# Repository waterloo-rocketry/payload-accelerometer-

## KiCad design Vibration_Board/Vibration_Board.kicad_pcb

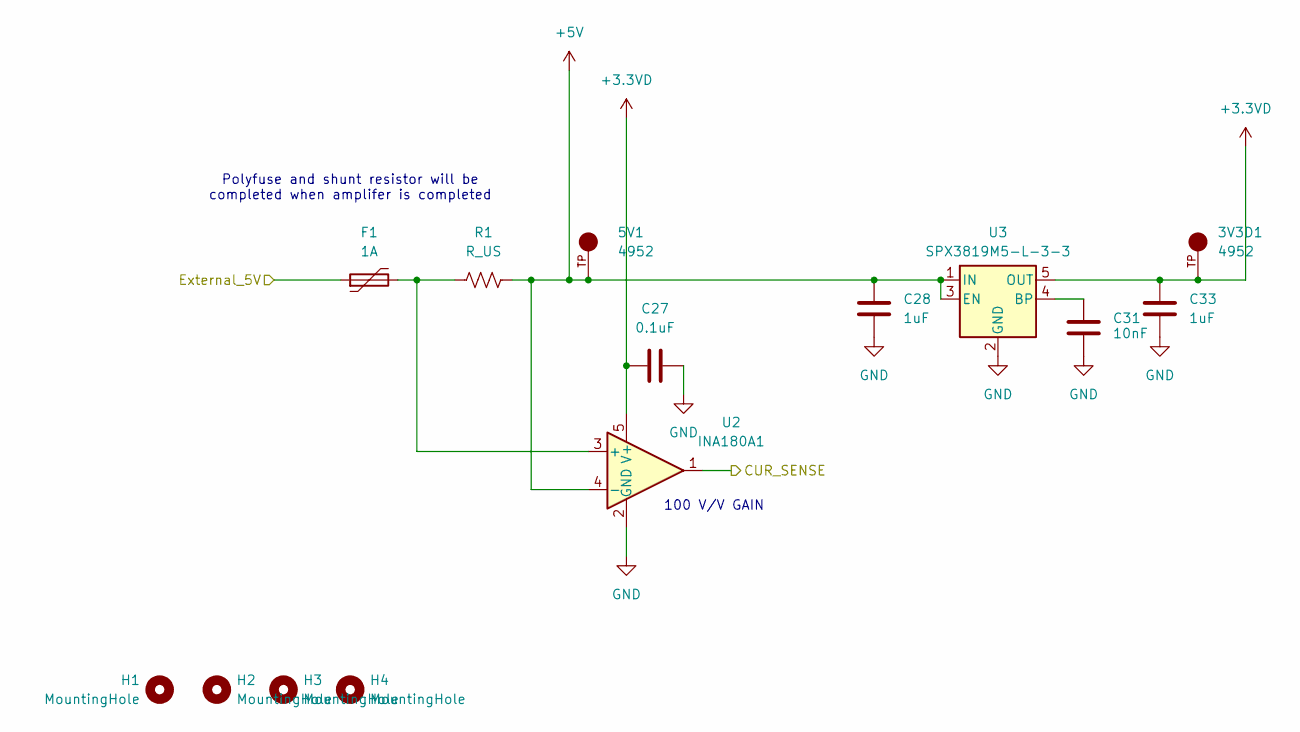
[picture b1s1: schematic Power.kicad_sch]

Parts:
3V3D1, 5V1: 4952; KEYSTONE_4952; PARTREV A
C27: 0.1uF; C_0805_2012Metric_Pad1.18x1.45mm_HandSolder
C28, C33: 1uF; C_0805_2012Metric_Pad1.18x1.45mm_HandSolder
C31: 10nF; C_0805_2012Metric_Pad1.18x1.45mm_HandSolder
F1: 1A; C_0805_2012Metric_Pad1.18x1.45mm_HandSolder
H1, H2, H3, H4: MountingHole; MountingHole_3.2mm_M3_ISO7380_Pad_TopBottom
R1: R_US; R_0805_2012Metric_Pad1.20x1.40mm_HandSolder
U2: INA180A1; SOT-23-5
U3: SPX3819M5-L-3-3; SOT-23-5

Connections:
+3.3VD: 3V3D1.TP, C27.1, C33.1, U2.5 (V+), U3.5 (OUT); also elsewhere on the board
+5V: 5V1.TP, C28.1, R1.2, U2.4 (-), U3.1 (IN), U3.3 (EN); also elsewhere on the board
/CUR_SEN: U2.1; also elsewhere on the board
/EXT_5V: F1.1; also elsewhere on the board
GND: C27.2, C28.2, C31.2, C33.2, U2.2 (GND), U3.2 (GND); also elsewhere on the board
unnamed: F1.2, R1.1, U2.3 (+)
unnamed: C31.1, U3.4 (BP)

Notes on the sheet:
100 V/V GAIN
Polyfuse and shunt resistor will be completed when amplifer is completed

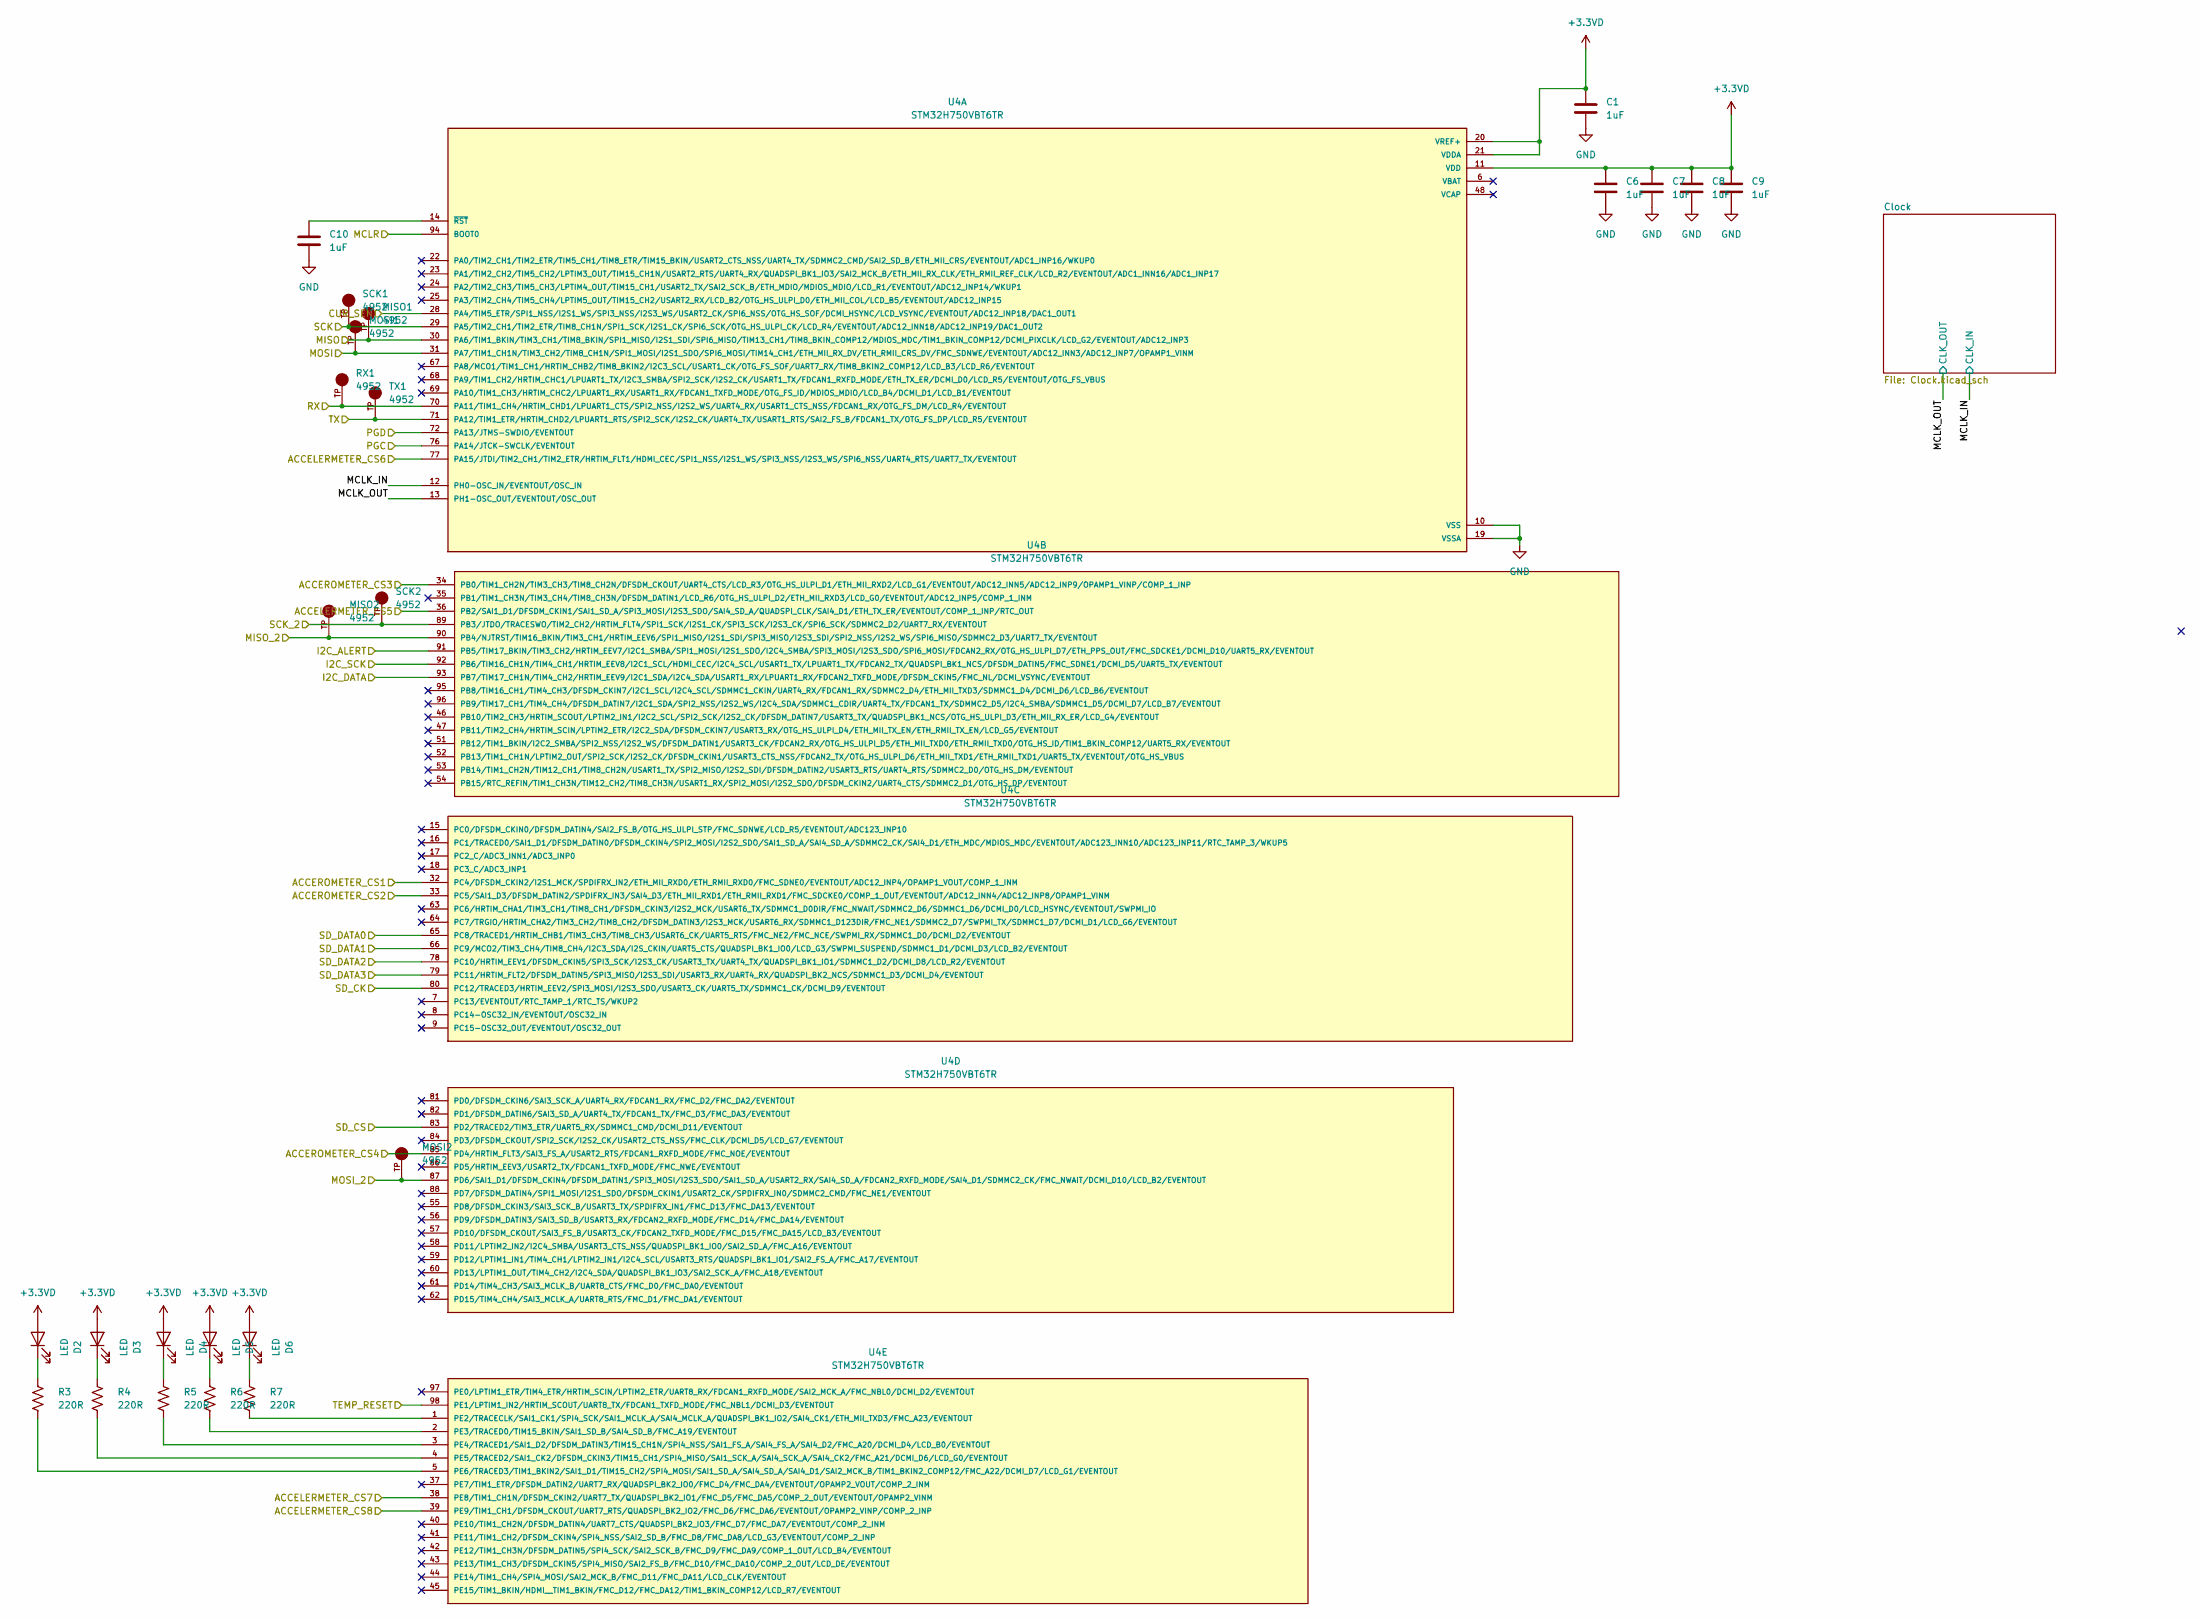
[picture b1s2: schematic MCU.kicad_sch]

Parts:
C1, C6, C7, C8, C9, C10: 1uF; C_0805_2012Metric_Pad1.18x1.45mm_HandSolder
D2, D3, D4, D5, D6: LED; LED_1206_3216Metric_Pad1.42x1.75mm_HandSolder
MISO1, MISO2: 4952; KEYSTONE_4952; PARTREV A
MOSI1, MOSI2: 4952; KEYSTONE_4952; PARTREV A
R3, R4, R5, R6, R7: 220R; R_0805_2012Metric_Pad1.20x1.40mm_HandSolder
RX1: 4952; KEYSTONE_4952; PARTREV A
SCK1, SCK2: 4952; KEYSTONE_4952; PARTREV A
TX1: 4952; KEYSTONE_4952; PARTREV A
U4: STM32H750VBT6TR; QFP50P1600X1600X160-100N; PARTREV 2

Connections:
+3.3VD: C1.1, C6.1, C7.1, C8.1, C9.1, D2.2 (A), D3.2 (A), D4.2 (A), D5.2 (A), D6.2 (A), U4.11 (VDD), U4.20 (VREF+), U4.21 (VDDA), U4.27 (VDD), U4.50 (VDD), U4.75 (VDD), U4.100 (VDD); also elsewhere on the board
/ACCEL_CS1: U4.32 (PC4/DFSDM_CKIN2/I2S1_MCK/SPDIFRX_IN2/ET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); also elsewhere on the board
/ACCEL_CS2: U4.33 (PC5/SAI1_D3/DFSDM_DATIN2/SPDIFRX_IN3/SA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); also elsewhere on the board
/ACCEL_CS3: U4.34 (PB0/TIM1_CH2N/TIM3_CH3/TIM8_CH2N/DFSDM_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); also elsewhere on the board
/ACCEL_CS4: U4.85 (PD4/HRTIM_FLT3/SAI3_FS_A/USART2_RTS/FDC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); also elsewhere on the board
/ACCEL_CS5: U4.36 (PB2/SAI1_D1/DFSDM_CKIN1/SAI1_SD_A/SPI3_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); also elsewhere on the board
/ACCEL_CS6: U4.77 (PA15/JTDI/TIM2_CH1/TIM2_ETR/HRTIM_FLT1/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); also elsewhere on the board
/ACCEL_CS7: U4.38 (PE8/TIM1_CH1N/DFSDM_CKIN2/UART7_TX/QUAD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); also elsewhere on the board
/ACCEL_CS8: U4.39 (PE9/TIM1_CH1/DFSDM_CKOUT/UART7_RTS/QUAD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); also elsewhere on the board
/CUR_SEN: U4.28 (PA4/TIM5_ETR/SPI1_NSS/I2S1_WS/SPI3_NSS/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); also elsewhere on the board
/Connectors/DATA1: U4.65 (PC8/TRACED1/HRTIM_CHB1/TIM3_CH3/TIM8_CH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); also elsewhere on the board
/Connectors/DATA2: U4.66 (PC9/MCO2/TIM3_CH4/TIM8_CH4/I2C3_SDA/I2S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); also elsewhere on the board
/Connectors/DATA3: U4.78 (PC10/HRTIM_EEV1/DFSDM_CKIN5/SPI3_SCK/I2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); also elsewhere on the board
/Connectors/DATA4: U4.79 (PC11/HRTIM_FLT2/DFSDM_DATIN5/SPI3_MISO/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); also elsewhere on the board
/Connectors/MISO_2: MISO2.TP, U4.90 (PB4/NJTRST/TIM16_BKIN/TIM3_CH1/HRTIM_EE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); also elsewhere on the board
/Connectors/MOSI_2: MOSI2.TP, U4.87 (PD6/SAI1_D1/DFSDM_CKIN4/DFSDM_DATIN1/SP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); also elsewhere on the board
/Connectors/SCK_2: SCK2.TP, U4.89 (PB3/JTDO/TRACESWO/TIM2_CH2/HRTIM_FLT4/S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); also elsewhere on the board
/Connectors/SD_CLK: U4.80 (PC12/TRACED3/HRTIM_EEV2/SPI3_MOSI/I2S3_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); also elsewhere on the board
/Connectors/SD_CS: U4.83 (PD2/TRACED2/TIM3_ETR/UART5_RX/SDMMC1_CM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); also elsewhere on the board
/I2C_ALERT: U4.91 (PB5/TIM17_BKIN/TIM3_CH2/HRTIM_EEV7/I2C1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); also elsewhere on the board
/I2C_DATA: U4.93 (PB7/TIM17_CH1N/TIM4_CH2/HRTIM_EEV9/I2C1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); also elsewhere on the board
/I2C_SCK: U4.92 (PB6/TIM16_CH1N/TIM4_CH1/HRTIM_EEV8/I2C1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); also elsewhere on the board
/MCLR: U4.94 (BOOT0); also elsewhere on the board
/MCU/MCLK_IN: U4.12 (PH0-OSC_IN/EVENTOUT/OSC_IN); also elsewhere on the board
/MCU/MCLK_OUT: U4.13 (PH1-OSC_OUT/EVENTOUT/OSC_OUT); also elsewhere on the board
/MISO: MISO1.TP, U4.30 (PA6/TIM1_BKIN/TIM3_CH1/TIM8_BKIN/SPI1_M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); also elsewhere on the board
/MOSI: MOSI1.TP, U4.31 (PA7/TIM1_CH1N/TIM3_CH2/TIM8_CH1N/SPI1_M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); also elsewhere on the board
/PGC: U4.72 (PA13/JTMS-SWDIO/EVENTOUT); also elsewhere on the board
/PGD: U4.76 (PA14/JTCK-SWCLK/EVENTOUT); also elsewhere on the board
/RX: RX1.TP, U4.70 (PA11/TIM1_CH4/HRTIM_CHD1/LPUART1_CTS/SP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); also elsewhere on the board
/SCK: SCK1.TP, U4.29 (PA5/TIM2_CH1/TIM2_ETR/TIM8_CH1N/SPI1_SC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); also elsewhere on the board
/SENSOR_RESET: U4.98 (PE1/LPTIM1_IN2/HRTIM_SCOUT/UART8_TX/FDC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); also elsewhere on the board
/TX: TX1.TP, U4.71 (PA12/TIM1_ETR/HRTIM_CHD2/LPUART1_RTS/SP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); also elsewhere on the board
GND: C1.2, C6.2, C7.2, C8.2, C9.2, C10.2, U4.10 (VSS), U4.19 (VSSA), U4.26 (VSS), U4.49 (VSS), U4.74 (VSS), U4.99 (VSS); also elsewhere on the board
unnamed: D2.1 (K), R3.1
unnamed: D3.1 (K), R4.1
unnamed: D4.1 (K), R5.1
unnamed: D5.1 (K), R6.1
unnamed: D6.1 (K), R7.1
unnamed: C10.1, U4.14 (~RST)
unnamed: R7.2, U4.1 (PE2/TRACECLK/SAI1_CK1/SPI4_SCK/SAI1_MCL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)
unnamed: R6.2, U4.2 (PE3/TRACED0/TIM15_BKIN/SAI1_SD_B/SAI4_S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)
unnamed: R5.2, U4.3 (PE4/TRACED1/SAI1_D2/DFSDM_DATIN3/TIM15_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)
unnamed: R4.2, U4.4 (PE5/TRACED2/SAI1_CK2/DFSDM_CKIN3/TIM15_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)
unnamed: R3.2, U4.5 (PE6/TRACED3/TIM1_BKIN2/SAI1_D1/TIM15_CH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)

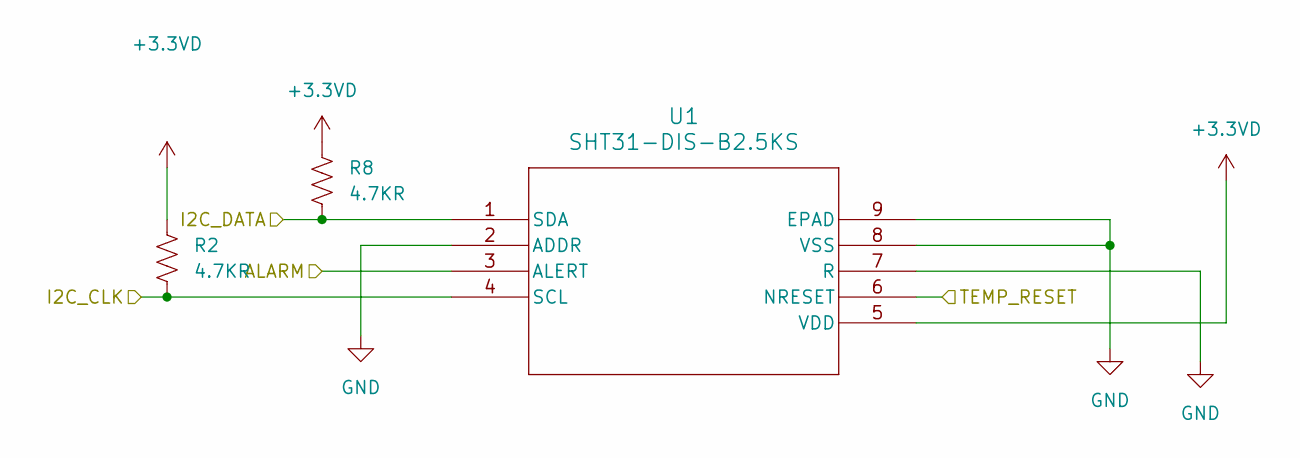
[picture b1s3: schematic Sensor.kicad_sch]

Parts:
R2, R8: 4.7KR; R_0805_2012Metric_Pad1.20x1.40mm_HandSolder
U1: SHT31-DIS-B2.5KS; U_SHT3_SEN-M

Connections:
+3.3VD: R2.1, R8.1, U1.5 (VDD); also elsewhere on the board
/I2C_ALERT: U1.3 (ALERT); also elsewhere on the board
/I2C_DATA: R8.2, U1.1 (SDA); also elsewhere on the board
/I2C_SCK: R2.2, U1.4 (SCL); also elsewhere on the board
/SENSOR_RESET: U1.6 (NRESET); also elsewhere on the board
GND: U1.2 (ADDR), U1.7 (R), U1.8 (VSS), U1.9 (EPAD); also elsewhere on the board

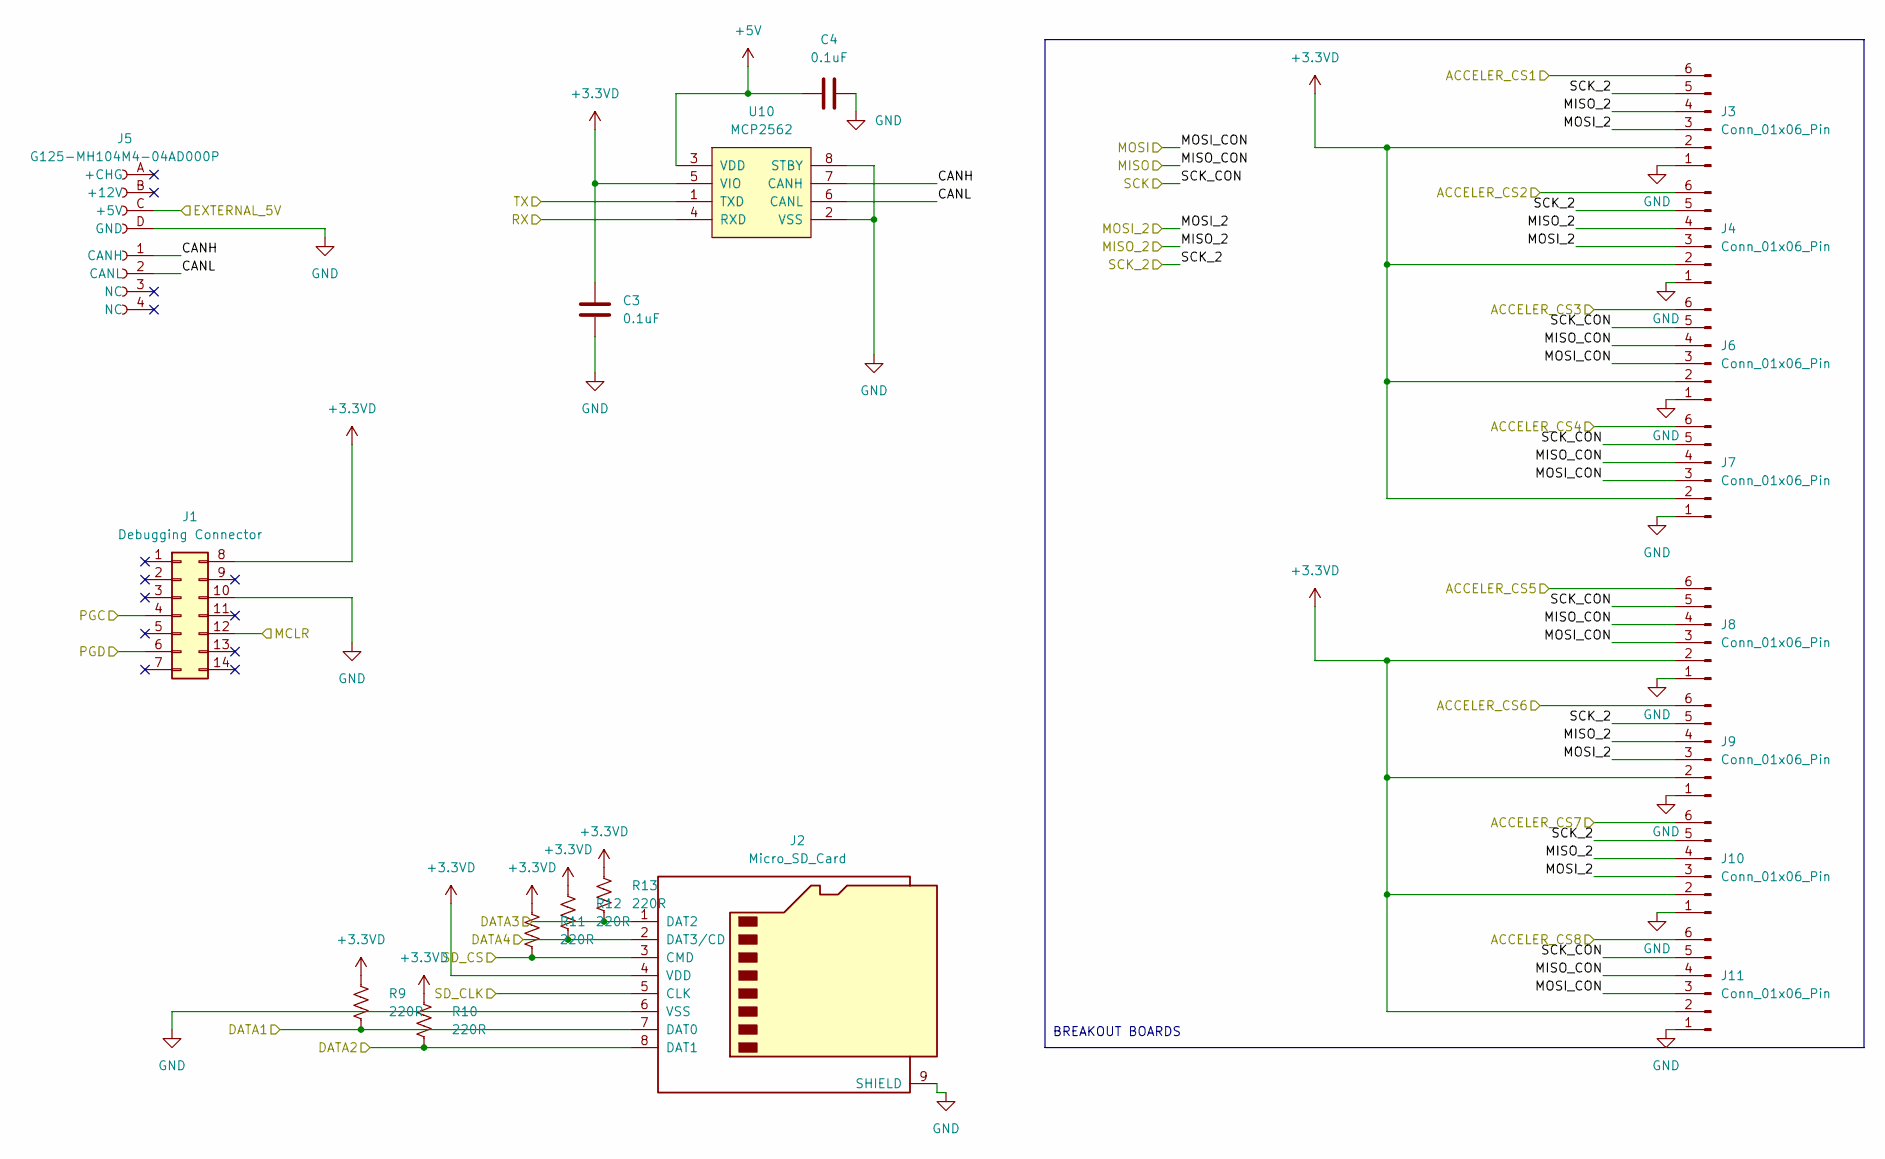
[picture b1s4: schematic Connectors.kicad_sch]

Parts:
C3, C4: 0.1uF; C_0805_2012Metric_Pad1.18x1.45mm_HandSolder
J1: Debugging Connector; PinHeader_2x07_P1.27mm_Vertical_SMD
J2: Micro_SD_Card; microSD_Molex_WM6698CT-ND
J3, J4, J6, J7, J8, J9, J10, J11: Conn_01x06_Pin; CONN6_S6B-PH_JST
J5: G125-MH104M4-04AD000P; connector_Harwin_G125-MH104M4-04AD000P
R9, R10, R11, R12, R13: 220R; R_0805_2012Metric_Pad1.20x1.40mm_HandSolder
U10: MCP2562; SOIC-8_3.9x4.9mm_P1.27mm

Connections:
+3.3VD: C3.2, J1.8, J2.4 (VDD), J3.2, J4.2, J6.2, J7.2, J8.2, J9.2, J10.2, J11.2, R9.1, R10.1, R11.1, R12.1, R13.1, U10.5 (VIO); also elsewhere on the board
+5V: C4.1, U10.3 (VDD); also elsewhere on the board
/ACCEL_CS1: J7.6; also elsewhere on the board
/ACCEL_CS2: J6.6; also elsewhere on the board
/ACCEL_CS3: J4.6; also elsewhere on the board
/ACCEL_CS4: J3.6; also elsewhere on the board
/ACCEL_CS5: J8.6; also elsewhere on the board
/ACCEL_CS6: J9.6; also elsewhere on the board
/ACCEL_CS7: J10.6; also elsewhere on the board
/ACCEL_CS8: J11.6; also elsewhere on the board
/Connectors/CANH: J5.1 (CANH), U10.7 (CANH)
/Connectors/CANL: J5.2 (CANL), U10.6 (CANL)
/Connectors/DATA1: J2.7 (DAT0), R9.2; also elsewhere on the board
/Connectors/DATA2: J2.8 (DAT1), R10.2; also elsewhere on the board
/Connectors/DATA3: J2.1 (DAT2), R13.2; also elsewhere on the board
/Connectors/DATA4: J2.2 (DAT3/CD), R12.2; also elsewhere on the board
/Connectors/MISO_2: J3.4, J4.4, J9.4, J10.4; also elsewhere on the board
/Connectors/MOSI_2: J3.3, J4.3, J9.3, J10.3; also elsewhere on the board
/Connectors/SCK_2: J3.5, J4.5, J9.5, J10.5; also elsewhere on the board
/Connectors/SD_CLK: J2.5 (CLK); also elsewhere on the board
/Connectors/SD_CS: J2.3 (CMD), R11.2; also elsewhere on the board
/EXT_5V: J5.C (+5V); also elsewhere on the board
/MCLR: J1.12; also elsewhere on the board
/MISO: J6.4, J7.4, J8.4, J11.4; also elsewhere on the board
/MOSI: J6.3, J7.3, J8.3, J11.3; also elsewhere on the board
/PGC: J1.4; also elsewhere on the board
/PGD: J1.6; also elsewhere on the board
/RX: U10.4 (RXD); also elsewhere on the board
/SCK: J6.5, J7.5, J8.5, J11.5; also elsewhere on the board
/TX: U10.1 (TXD); also elsewhere on the board
GND: C3.1, C4.2, J1.10, J2.6 (VSS), J2.9 (SHIELD), J3.1, J4.1, J5.D (GND), J6.1, J7.1, J8.1, J9.1, J10.1, J11.1, U10.2 (VSS), U10.8 (STBY); also elsewhere on the board

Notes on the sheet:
BREAKOUT BOARDS

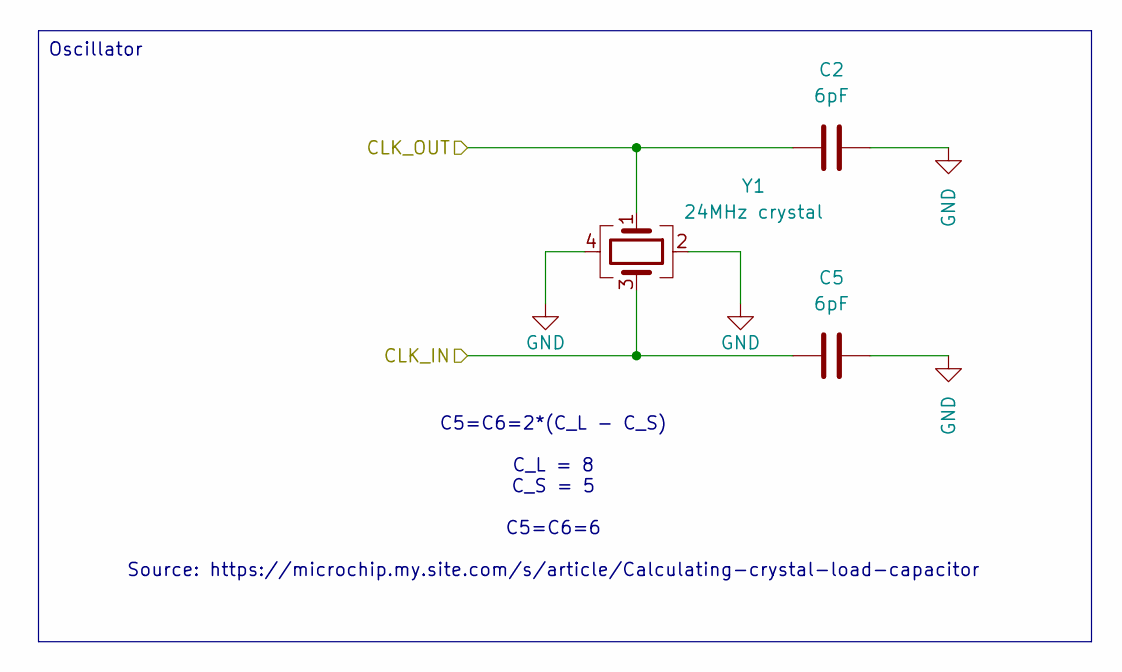
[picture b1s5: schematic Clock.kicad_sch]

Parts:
C2, C5: 6pF; C_0603_1608Metric_Pad1.08x0.95mm_HandSolder
Y1: 24MHz crystal; Crystal_SMD_Abracon_ABM8G-4Pin_3.2x2.5mm

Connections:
/MCU/MCLK_IN: C5.1, Y1.3; also elsewhere on the board
/MCU/MCLK_OUT: C2.2, Y1.1; also elsewhere on the board
GND: C2.1, C5.2, Y1.2, Y1.4; also elsewhere on the board

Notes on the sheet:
C5=C6=2*(C_L - C_S) C_L = 8 C_S = 5 C5=C6=6 Source: https://microchip.my.site.com/s/article/Calculating-crystal-load-capacitor
Oscillator

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
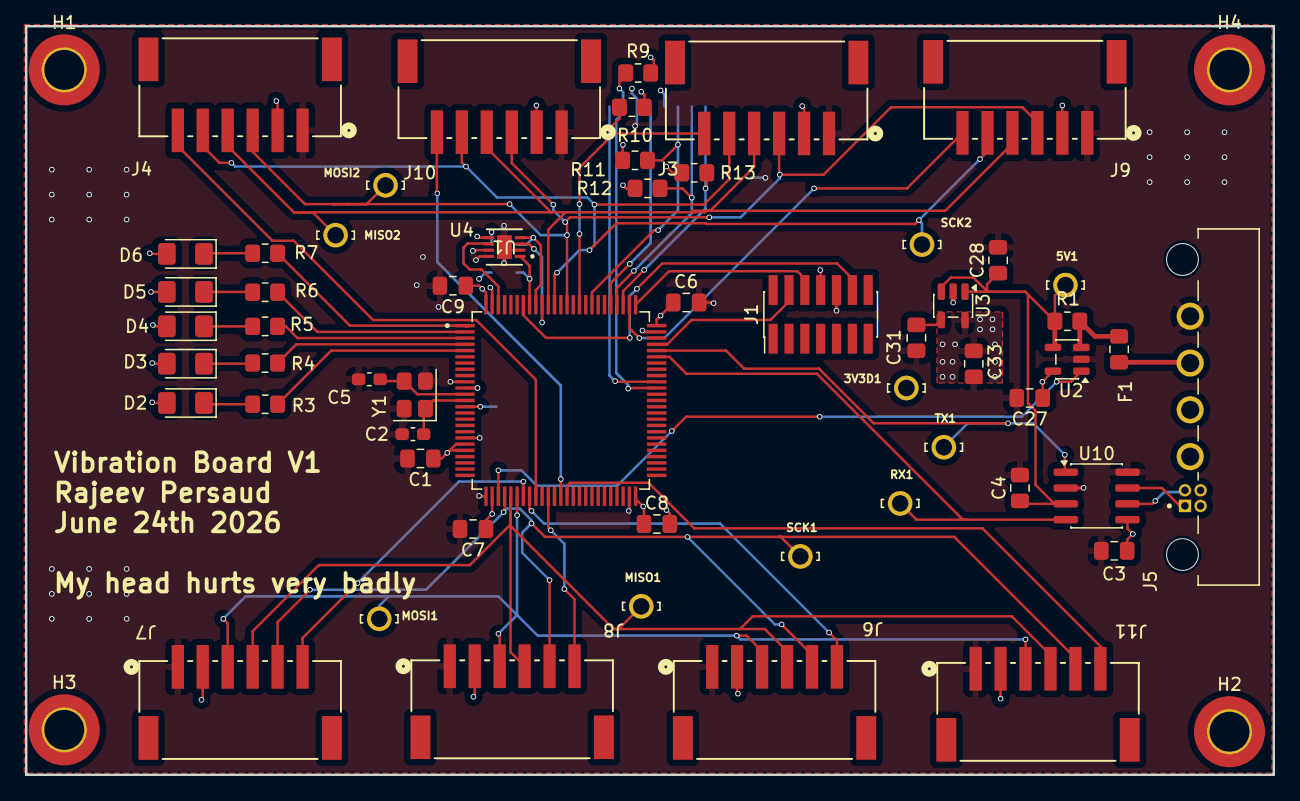
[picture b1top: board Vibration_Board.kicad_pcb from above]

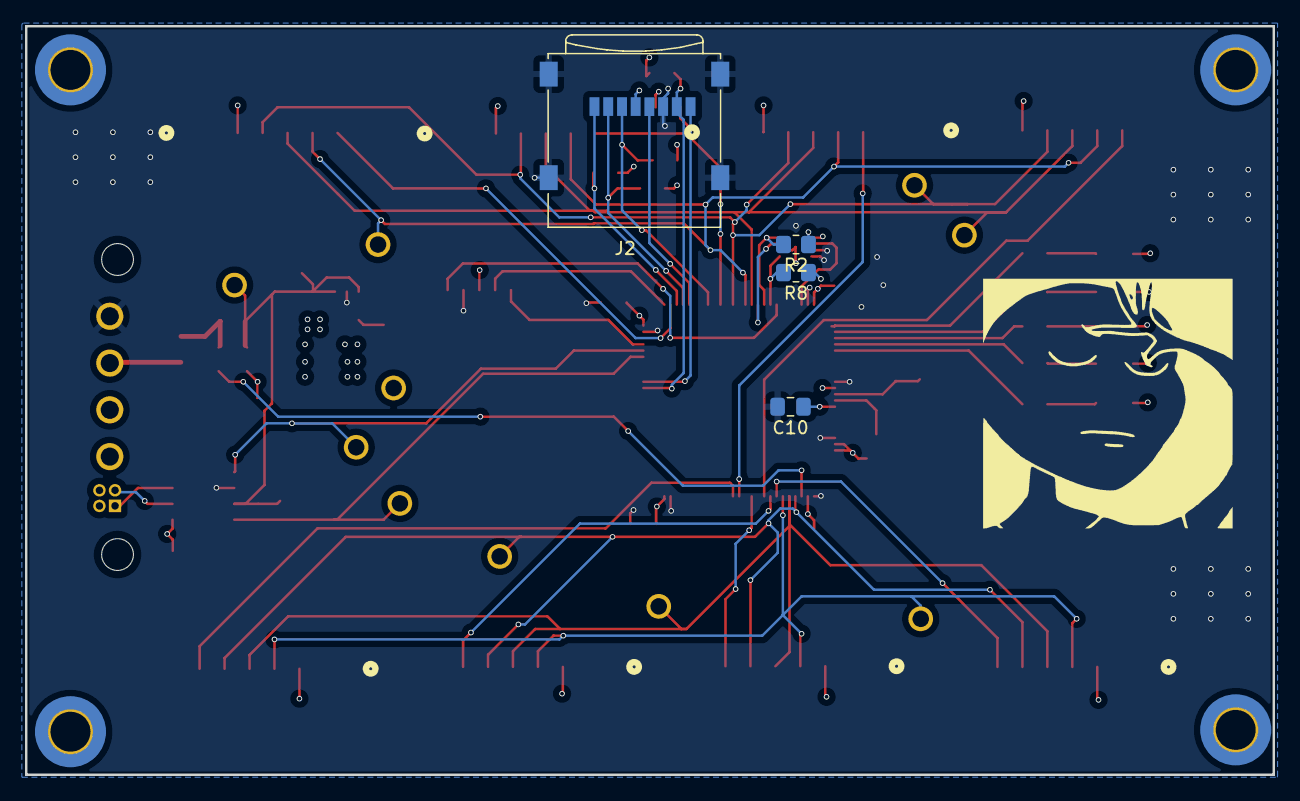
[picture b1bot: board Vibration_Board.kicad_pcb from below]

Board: 4 copper layers, 100.0 x 60.0 mm, 64 parts (4 on the bottom side), 51 nets.

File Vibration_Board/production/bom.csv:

Designator,Footprint,Quantity,Value,LCSC Part #
"3V3D1, 5V1, MISO1, MISO2, MOSI1, MOSI2, RX1, SCK1, SCK2, TX1",KEYSTONE_4952,10,4952,
"C1, C10, C28, C33, C6, C7, C8, C9",0805,8,1uF,
"C2, C5",0603,2,6pF,
"C27, C3, C4",0805,3,0.1uF,
C31,0805,1,10nF,
"D2, D3, D4, D5, D6",1206,5,LED,
F1,0805,1,1A,
J1,PinHeader_2x07_P1.27mm_Vertical_SMD,1,Debugging Connector,
"J10, J11, J3, J4, J6, J7, J8, J9",CONN6_S6B-PH_JST,8,Conn_01x06_Pin,
J2,microSD_Molex_WM6698CT-ND,1,Micro_SD_Card,
J5,connector_Harwin_G125-MH104M4-04AD000P,1,G125-MH104M4-04AD000P,
R1,0805,1,R_US,
"R10, R11, R12, R13, R3, R4, R5, R6, R7, R9",0805,10,220R,
"R2, R8",0805,2,4.7KR,
U1,U_SHT3_SEN-M,1,SHT31-DIS-B2.5KS,
U10,SOIC-8_3.9x4.9mm_P1.27mm,1,MCP2562,
U2,SOT-23-5,1,INA180A1,
U3,SOT-23-5,1,SPX3819M5-L-3-3,
U4,QFP50P1600X1600X160-100N,1,STM32H750VBT6TR,
Y1,Crystal_SMD_Abracon_ABM8G-4Pin_3.2x2.5mm,1,24MHz crystal,

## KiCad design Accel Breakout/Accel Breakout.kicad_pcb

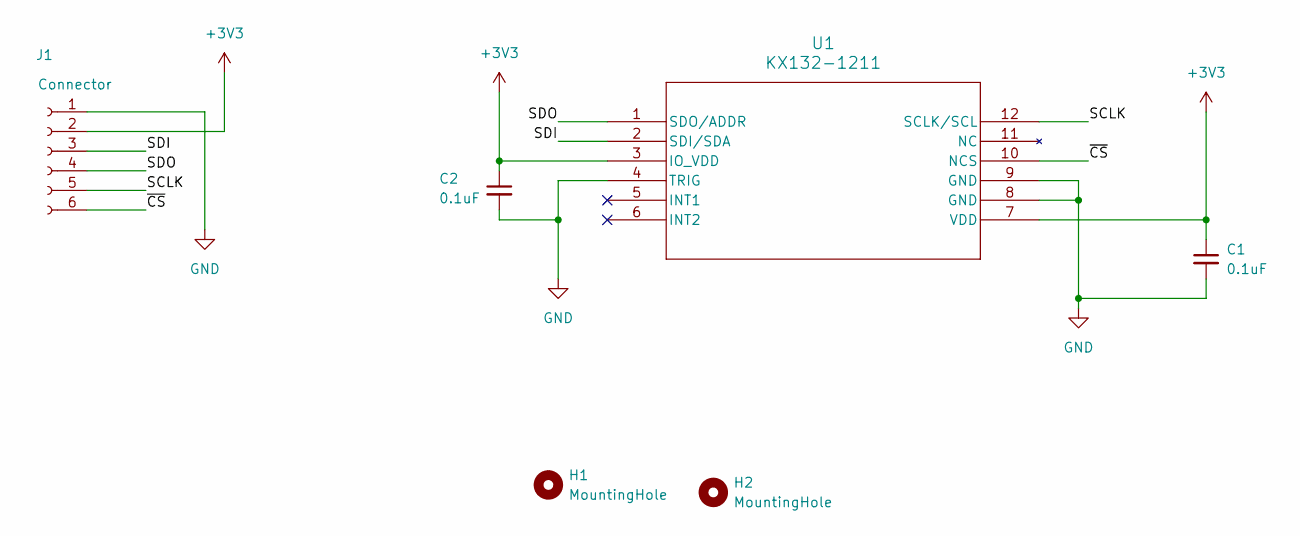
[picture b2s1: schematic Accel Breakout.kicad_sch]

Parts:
C1, C2: 0.1uF; C_0603_1608Metric_Pad1.08x0.95mm_HandSolder
H1, H2: MountingHole; MountingHole_3.2mm_M3
J1: Connector; JST_PH_S6B-PH-SM4-TB_1x06-1MP_P2.00mm_Horizontal
U1: KX132-1211; KX132-1211_KNX

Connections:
+3V3: C1.1, C2.1, J1.2, U1.3 (IO_VDD), U1.7 (VDD)
/SCLK: J1.5, U1.12 (SCLK/SCL)
/SDI: J1.3, U1.2 (SDI/SDA)
/SDO: J1.4, U1.1 (SDO/ADDR)
/~CS: J1.6, U1.10 (NCS)
GND: C1.2, C2.2, J1.1, U1.4 (TRIG), U1.8 (GND), U1.9 (GND)

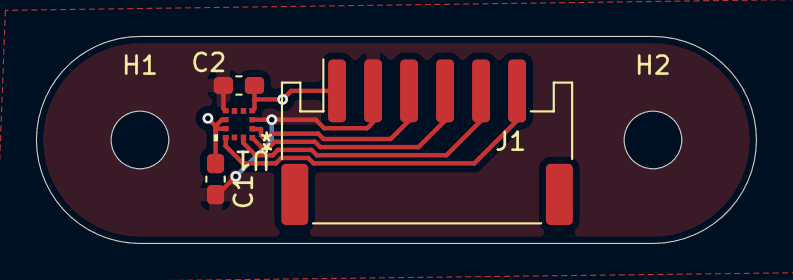
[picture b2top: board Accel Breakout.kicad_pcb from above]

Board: 2 copper layers, 40.0 x 11.5 mm, 6 parts (0 on the bottom side), 6 nets.

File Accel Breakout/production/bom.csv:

Designator,Footprint,Quantity,Value,LCSC Part #
"C1, C2",0603,2,0.1uF,
J1,JST_PH_S6B-PH-SM4-TB_1x06-1MP_P2.00mm_Horizontal,1,Connector,
U1,KX132-1211_KNX,1,KX132-1211,

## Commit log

2026-06-08 Completed sxhematic of main board
2026-06-24 everything added
2026-06-24 smell change
2026-06-24 changed wire dimension
2026-06-24 build files,bom and jlc bom
2026-06-25 Add breakout
2026-06-25 fixes from review
2026-06-25 layer problem for exporting
